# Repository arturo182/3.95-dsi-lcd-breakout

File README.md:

# 3.95" DSI LCD <-> Pine A64 Adapter

This a adapter board for the MTF0395SVN-02A LCD to the Pine A64 board.

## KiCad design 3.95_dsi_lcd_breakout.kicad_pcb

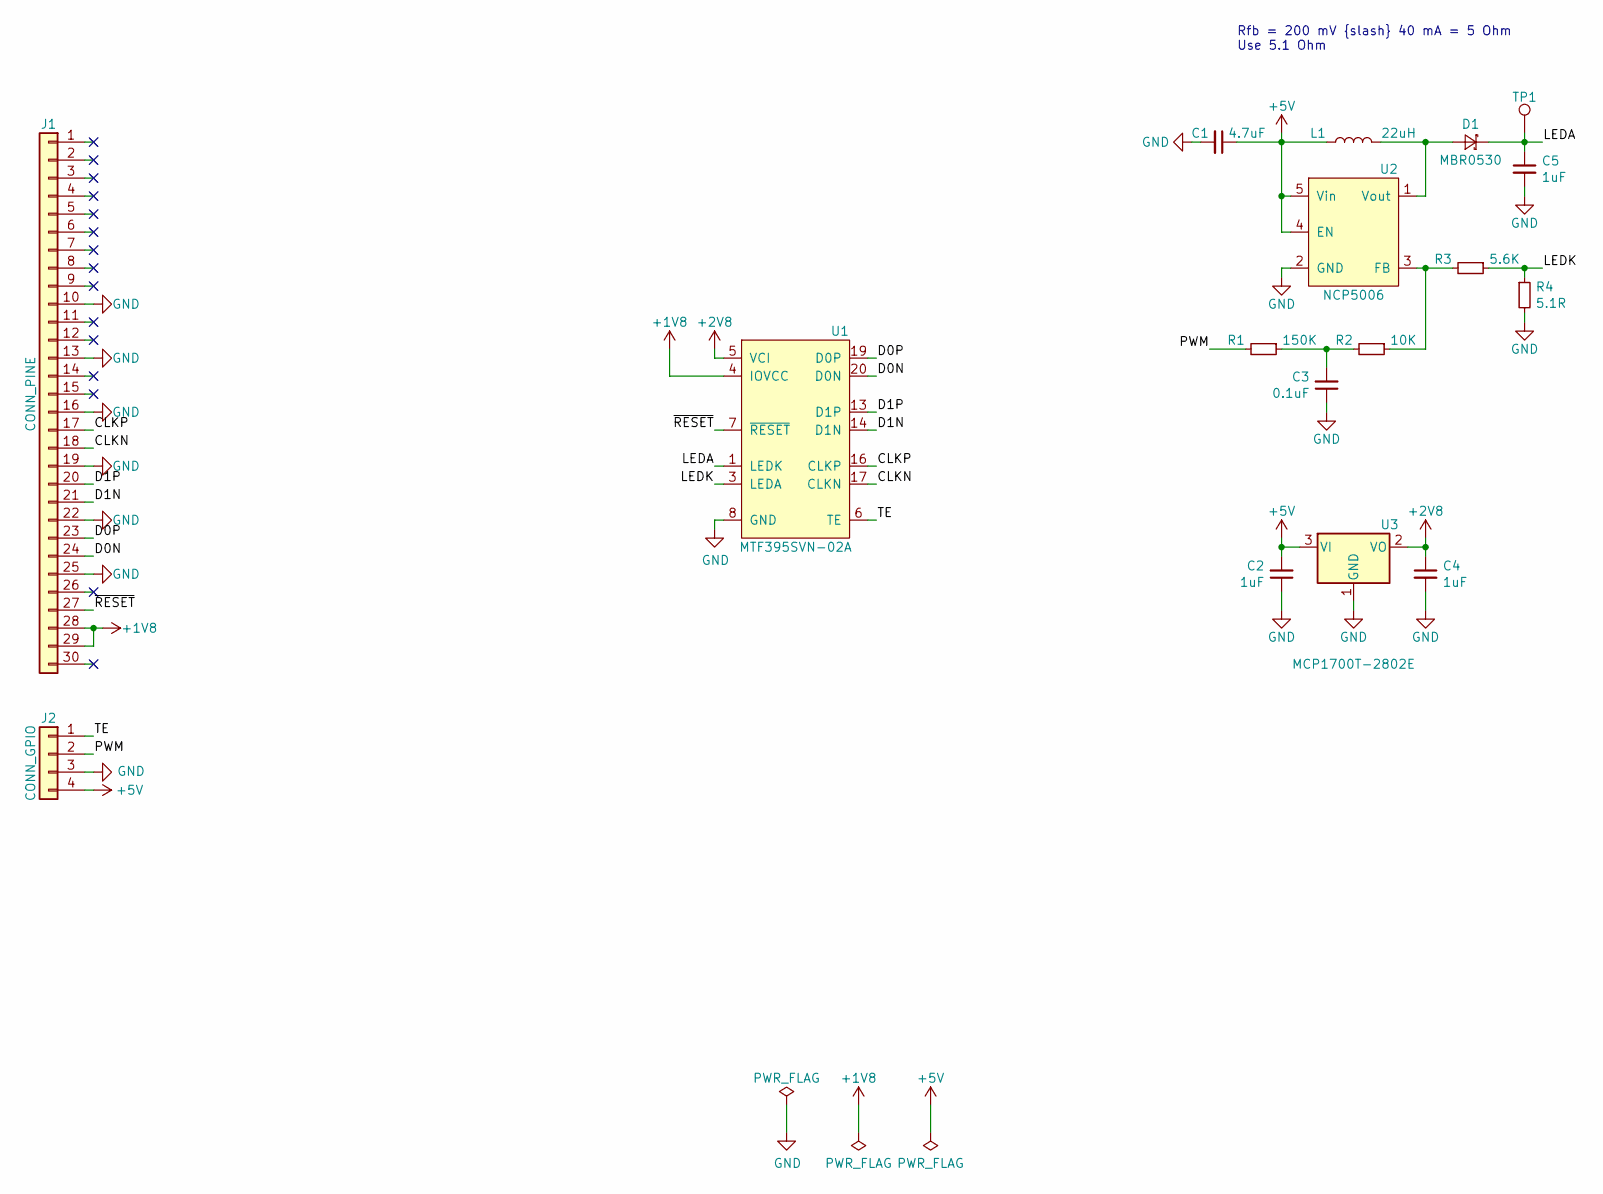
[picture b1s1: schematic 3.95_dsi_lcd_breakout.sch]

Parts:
C1: 4.7uF; C_0603_1608Metric
C2, C4, C5: 1uF; C_0603_1608Metric
C3: 0.1uF; C_0603_1608Metric
D1: MBR0530; D_SOD-123
J1: CONN_PINE; 10051922-3010EHLF_1x30-1MP_P0.50mm_Horizontal
J2: CONN_GPIO; PinHeader_1x04_P2.54mm_Vertical
L1: 22uH; L_Wuerth_WE-TPC-3816
R1: 150K; R_0603_1608Metric
R2: 10K; R_0603_1608Metric
R3: 5.6K; R_0603_1608Metric
R4: 5.1R; R_0603_1608Metric
TP1: TP_LEDA; TestPoint_Pad_D1.5mm
U1: MTF395SVN-02A; 10051922-3010EHLF_1x30-1MP_P0.50mm_Horizontal
U2: NCP5006; SOT-23-5
U3: MCP1700T-2802E; SOT-23

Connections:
+1V8: J1.28, J1.29, U1.4 (IOVCC)
+2V8: C4.1, U1.5 (VCI), U3.2 (VO)
+5V: C1.1, C2.2, J2.4, L1.2, U2.4 (EN), U2.5 (Vin), U3.3 (VI)
/CLKN: J1.18, U1.17 (CLKN)
/CLKP: J1.17, U1.16 (CLKP)
/D0N: J1.24, U1.20 (D0N)
/D0P: J1.23, U1.19 (D0P)
/D1N: J1.21, U1.14 (D1N)
/D1P: J1.20, U1.13 (D1P)
/LEDA: C5.1, D1.1 (K), TP1.1, U1.1 (LEDK), U1.2 (LEDK)
/LEDK: R3.1, R4.1, U1.3 (LEDA)
/PWM: J2.2, R1.2
/TE: J2.1, U1.6 (TE)
/~RESET~: J1.27, U1.7 (~RESET~)
GND: C1.2, C2.1, C3.1, C4.2, C5.2, J1.10, J1.13, J1.16, J1.19, J1.22, J1.25, J2.3, R4.2, U1.8 (GND), U1.9 (GND), U1.12 (GND), U1.15 (GND), U1.18 (GND), U1.21 (GND), U1.24 (GND), U1.30 (GND), U2.2 (GND), U3.1 (GND)
unnamed: C3.2, R1.1, R2.2
unnamed: D1.2 (A), L1.1, U2.1 (Vout)
unnamed: R2.1, R3.2, U2.3 (FB)

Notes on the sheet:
Rfb = 200 mV {slash} 40 mA = 5 Ohm Use 5.1 Ohm

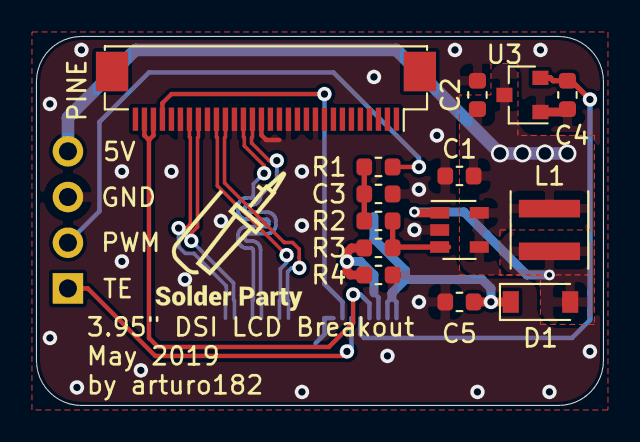
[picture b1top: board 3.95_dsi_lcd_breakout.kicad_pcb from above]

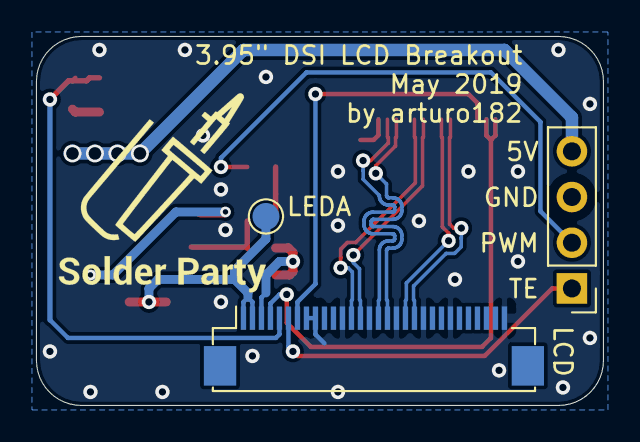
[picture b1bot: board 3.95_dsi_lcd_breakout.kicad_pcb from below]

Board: 2 copper layers, 31.5 x 20.5 mm, 17 parts (3 on the bottom side), 18 nets.

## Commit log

2019-05-01 Initial import
